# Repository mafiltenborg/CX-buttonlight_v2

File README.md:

# CX-buttonlight_v2

Better version of the LED lightsource for buttons in your [Citroën CX](https://en.wikipedia.org/wiki/Citro%C3%ABn_CX).

Building on the learnings from [its predecessor](https://github.com/mafiltenborg/CX_buttonlight), the improved version of this little lightsource adds drop-in placement without the need for neither wiring nor the plastic housing from the existing Citroën part. This enables more light or less powerdraw as required by the user. Also, the light module becomes a whole lot easier to manufacture and put in its final position. This version, however, breaks all the originality because it is a component replacement, not a consumables replacement.

Because this device does not use the OE bulb holder (made out of yellow plastic) it allows for the use of any colour LED you fancy. The green light in the ashtray and the green light near the ignition key and the green light emanating from the dashboard computer can now be accompanied by green light from the buttons, making a unison expression. Some might want that...

Update: This device has now been superseded with  one that uses a different LED driving principle (constant current) and even lower power consumption. Go to [CX buttonlight v3](https://github.com/mafiltenborg/cx_buttonlight_v3) to learn more.

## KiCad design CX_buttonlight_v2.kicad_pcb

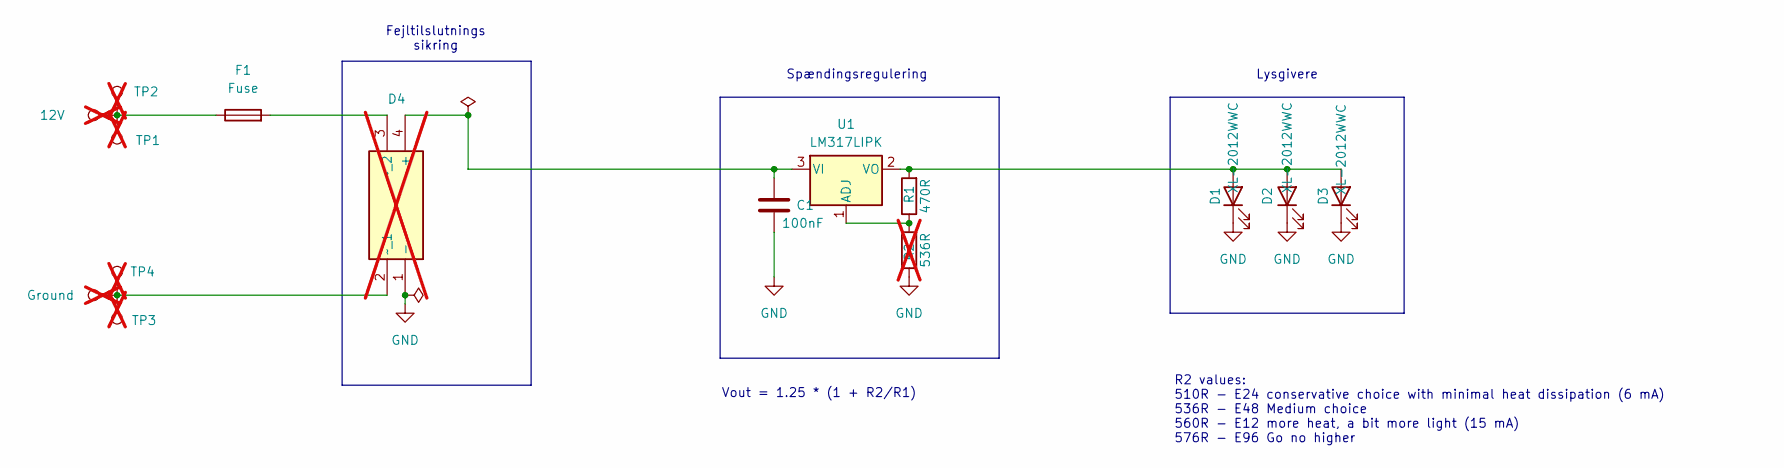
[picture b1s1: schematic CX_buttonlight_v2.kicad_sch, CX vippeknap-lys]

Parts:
C1: 100nF; C_0805_2012Metric_Pad1.18x1.45mm_HandSolder; LCSC Part # C49678
D1, D2, D3: XL-2012WWC; LED_0805_2012Metric_Pad1.15x1.40mm_HandSolder; LCSC Part # C965820
D4: BAS4002ARPPE6327HTSA1; Manufacturer_Part_Number BAS4002ARPPE6327HTSA1; Mouser Part Number 726-BAS4002ARPPE6; not fitted
F1: Fuse; Fuse_0805_2012Metric_Pad1.15x1.40mm_HandSolder
Ground1: Ground; TestPoint_THTPad_D1.5mm_Drill0.7mm; not fitted
R1: 470R; R_0805_2012Metric_Pad1.20x1.40mm_HandSolder; LCSC Part # C114564
R2: 536R; R_0805_2012Metric_Pad1.20x1.40mm_HandSolder; not fitted
Supply1: 12V; TestPoint_THTPad_D1.5mm_Drill0.7mm; not fitted
TP1, TP2, TP3, TP4: TestPoint; TestPoint_THTPad_D1.5mm_Drill0.7mm; not fitted
U1: LM317LIPK; SOT-89-3; LCSC Part # C112537

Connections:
GND: C1.2, D1.1 (K), D2.1 (K), D3.1 (K), D4.1 (-), R2.1
unnamed: D1.2 (A), D2.2 (A), D3.2 (A), R1.2, U1.2 (VO)
unnamed: C1.1, D4.4 (+), U1.3 (VI)
unnamed: D4.2 (~_1), Ground1.1, TP3.1, TP4.1
unnamed: D4.3 (~_2), F1.2
unnamed: F1.1, Supply1.1, TP1.1, TP2.1
unnamed: R1.1, R2.2, U1.1 (ADJ)

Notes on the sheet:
Fejltilslutnings sikring
R2 values: 510R - E24 conservative choice with minimal heat dissipation (6 mA) 536R - E48 Medium choice 560R - E12 more heat, a bit more light (15 mA) 576R - E96 Go no higher
Vout = 1.25 * (1 + R2/R1)
Lysgivere
Spændingsregulering

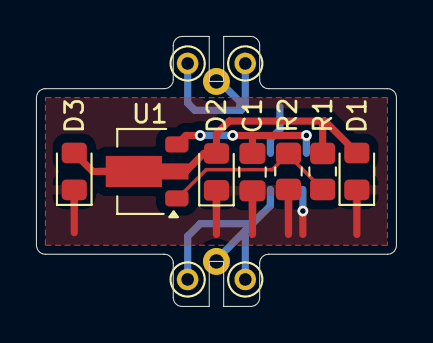
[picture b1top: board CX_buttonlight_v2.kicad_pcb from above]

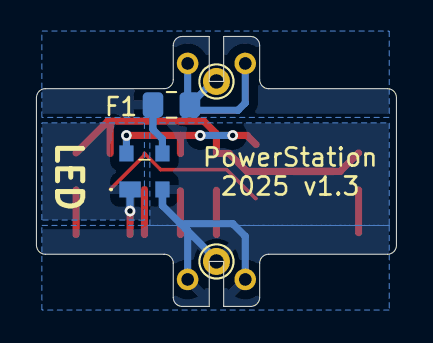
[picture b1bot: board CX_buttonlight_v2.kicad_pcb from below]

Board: 2 copper layers, 20.0 x 15.0 mm, 15 parts (4 on the bottom side), 7 nets.

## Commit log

2026-02-13 Update README.md
    Bad link detected
2026-02-13 Fuse added, minor fix in link given in README.md fixed
2026-02-13 Link to successor-project added.
2026-02-13 Added link was bad. Fixed to point FORWARD rather than BACK
